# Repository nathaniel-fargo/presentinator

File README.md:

# the PRESENTINATOR

## Plot
Santa got a cold, and it's December 24th! As his top elf you gotta step it up\
You decide to make a cannon to launch presents from the North Pole all over the world.\
Each house will light up when it's clock strikes midnight and you must shoot your target to the correct one.\
The longer you hold the trigger, the further your present will be shot. You call it, "the PRESENTINATOR".\
(Depending on how well this goes, you might be in for a raise aftewards... and boy do you love Candy Canes)

## Project

There's hardware, graphics, and soon to be firmware in this repo.\
I initially designed this as a four layer board, but when I experimenting with deleting the inner layers, practically all the grounds were routed together besides a few floating islands. Everything should be low speed enough so that's fine.\
The project is powered off of two 2032s, with a switch, and then minimal polarity protection and then bucked down to 3.3V.\
The brains of the operation is the STM32F030F4, a very minimal STM microcontroller.\
Over I2C it drives the IS31FL3731-SA LED Matrix driver, which is not used to full capacity.\
There's also a capactive sense button IC, as well as the capability to drive a vibration motor for full haptic I/O.

## Status
Hardware: Designed\
Board: Being manufactured\
Firmware: Will be done by Christmas

## License
MIT Open Source License-inator

## Motivation
I have some younger people in my life and a habit of making DIY christmas presents. In the past they've been largely "crafty" (e.g. wood, leather) but this year I went all-in on electronics.

## Inspiration
Roughly inspired by the [light rail](https://github.com/nonik0/Light-Rail) PCB train track project, as well as Doofenshmirtz's naming conventions.

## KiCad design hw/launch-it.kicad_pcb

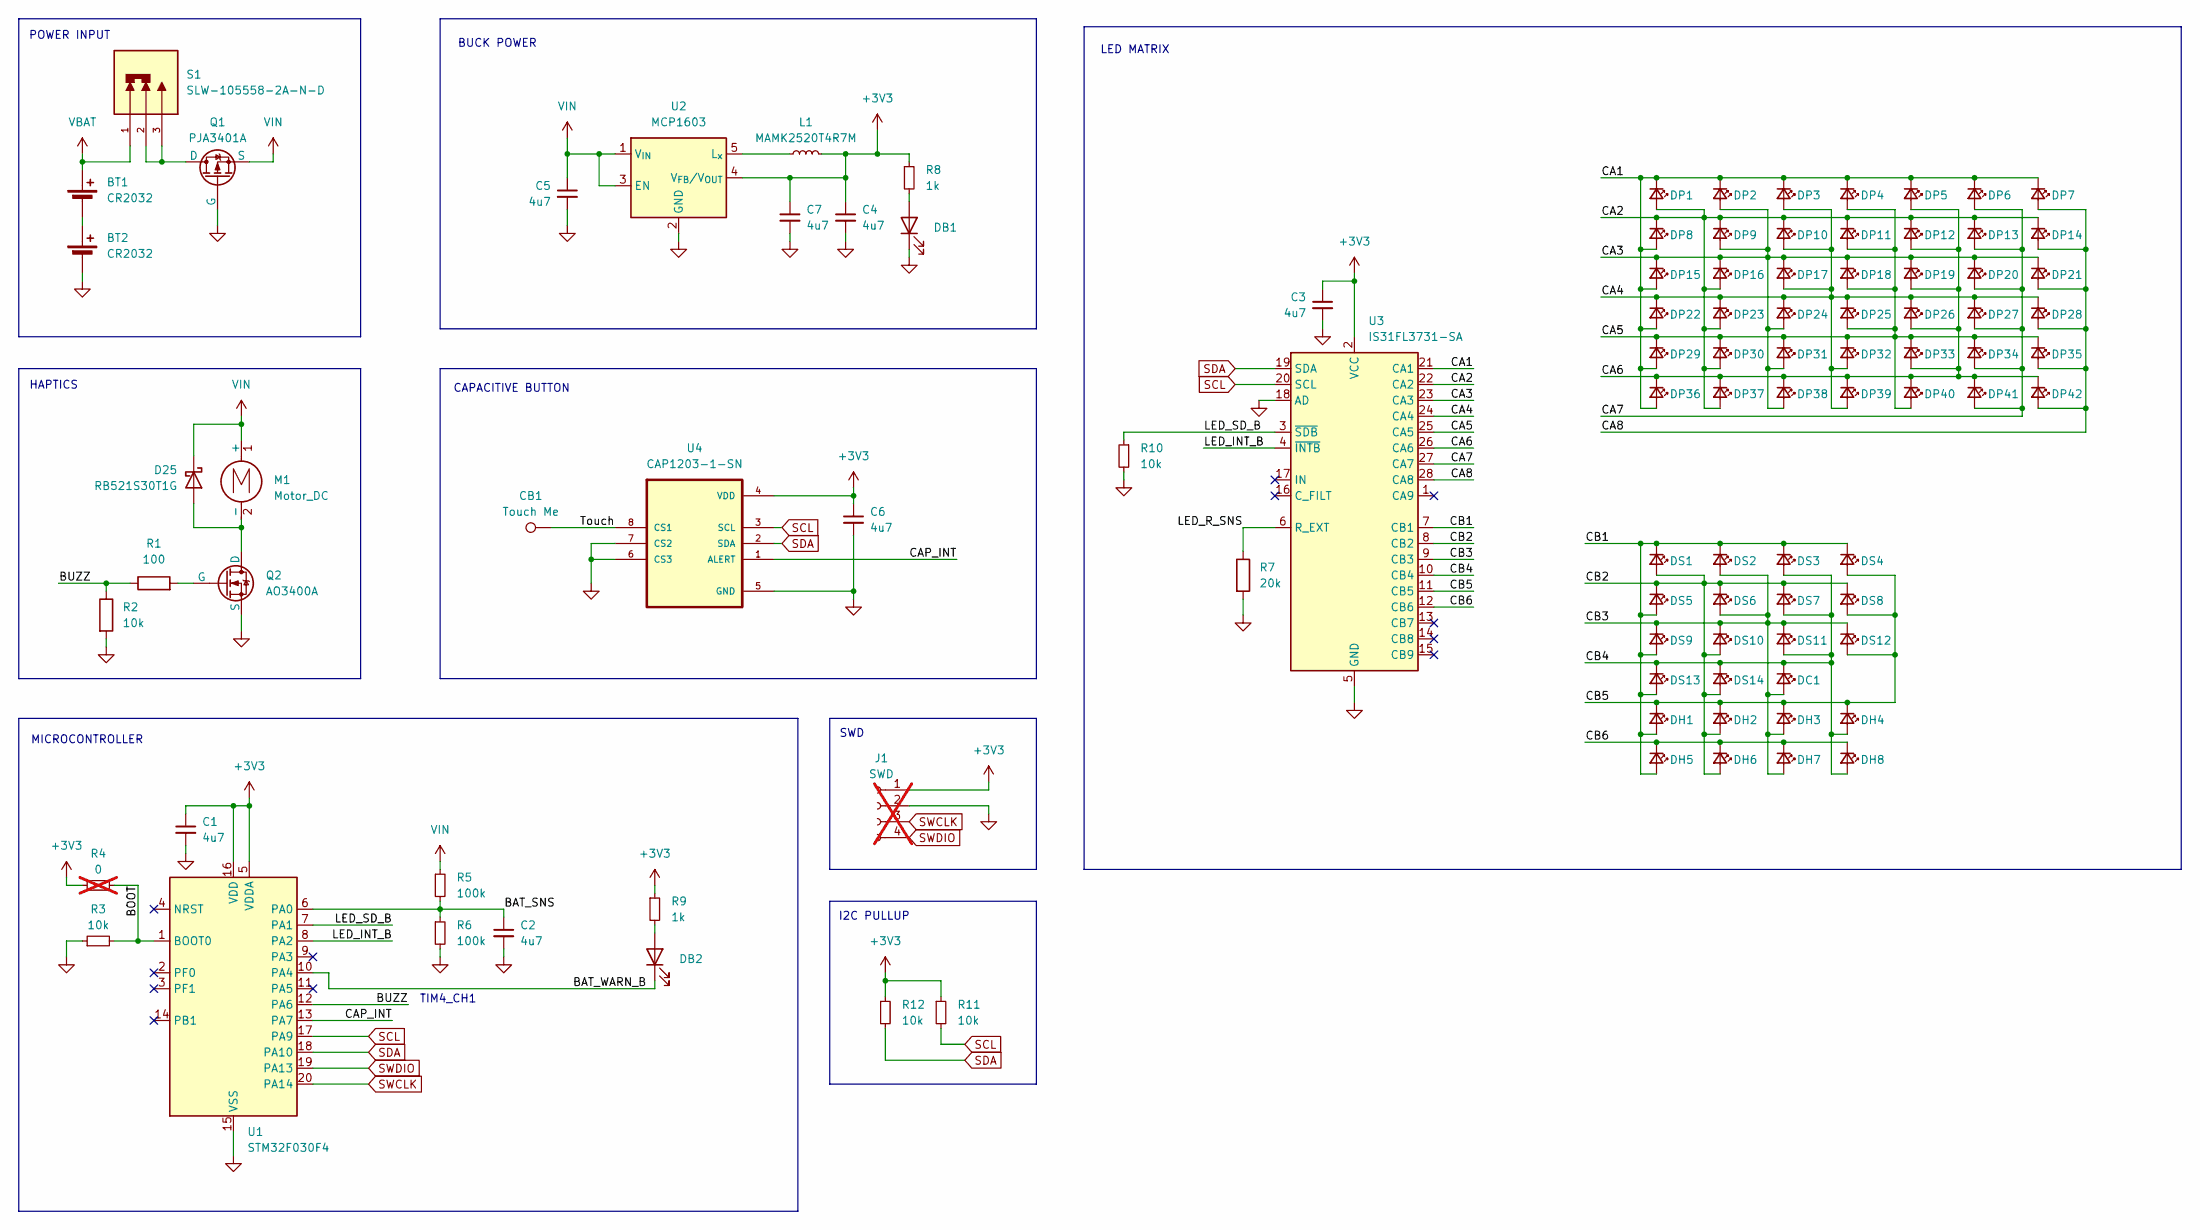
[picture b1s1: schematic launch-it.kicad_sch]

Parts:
BT1, BT2: CR2032; BAT_BAT-HLD-003-SMT
C1, C2, C3, C4, C5, C6, C7: 4u7; C_0402_1005Metric_Pad0.74x0.62mm_HandSolder
CB1: Touch Me; TestPoint_Pad_1.0x1.0mm
D25: RB521S30T1G; D_SOD-523
DB1, DB2: LED; LED_0805_2012Metric_InnerMarking
DC1: LED_Small; LED_0805_2012Metric_InnerMarking
DH1, DH2, DH3, DH4, DH5, DH6, DH7, DH8: LED_Small; LED_0805_2012Metric_InnerMarking
DP1, DP2, DP3, DP4, DP5, DP6, DP7, DP8, DP9, DP10, DP11, DP12, DP13, DP14, DP15, DP16, DP17, DP18, DP19, DP20, DP21, DP22, DP23, DP24, DP25, DP26, DP27, DP28, DP29, DP30, DP31, DP32, DP33, DP34, DP35, DP36, DP37, DP38, DP39, DP40, DP41, DP42: LED_Small; LED_0805_2012Metric_InnerMarking
DS1, DS2, DS3, DS4, DS5, DS6, DS7, DS8, DS9, DS10, DS11, DS12, DS13, DS14: LED_Small; LED_0402_1005Metric_Minimal
J1: SWD; PinHeader_1x04_P2.54mm_Vertical; not fitted
L1: MAMK2520T4R7M; L_1008_2520Metric_Pad1.43x2.20mm_HandSolder
M1: Motor_DC; PinHeader_1x02_P2.54mm_Vertical
Q1: PJA3401A; SOT-23-3
Q2: AO3400A; SOT-23-3
R1: 100; R_0402_1005Metric_Pad0.72x0.64mm_HandSolder
R2, R3, R10, R11, R12: 10k; R_0402_1005Metric_Pad0.72x0.64mm_HandSolder
R4: 0; R_0402_1005Metric_Pad0.72x0.64mm_HandSolder; not fitted
R5, R6: 100k; R_0402_1005Metric_Pad0.72x0.64mm_HandSolder
R7: 20k; R_0402_1005Metric_Pad0.72x0.64mm_HandSolder
R8, R9: 1k; R_0402_1005Metric_Pad0.72x0.64mm_HandSolder
S1: SLW-105558-2A-N-D; SW_SLW-105558-2A-N-D; PARTREV 1.01
U1: STM32F030F4; TSSOP-20_4.4x6.5mm_P0.65mm
U2: MCP1603; TSOT-23-5
U3: IS31FL3731-SA; SSOP-28_5.3x10.2mm_P0.65mm
U4: CAP1203-1-SN; SOIC127P600X175-8N

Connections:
+3V3: C1.1, C3.1, C4.1, C6.1, C7.1, J1.1, L1.2, R4.1, R8.1, R9.1, R11.1, R12.1, U1.5 (VDDA), U1.16 (VDD), U2.4 (V_{FB}/V_{OUT}), U3.2 (VCC), U4.4 (VDD)
/BAT_SNS: C2.1, R5.2, R6.1, U1.6 (PA0)
/BAT_WARN_B: DB2.1 (K), U1.10 (PA4)
/BOOT: R3.2, R4.2, U1.1 (BOOT0)
/BUZZ: R1.1, R2.1, U1.12 (PA6)
/CA1: DP1.1 (K), DP2.1 (K), DP3.1 (K), DP4.1 (K), DP5.1 (K), DP6.1 (K), DP7.1 (K), DP8.2 (A), DP15.2 (A), DP22.2 (A), DP29.2 (A), DP36.2 (A), U3.21 (CA1)
/CA2: DP1.2 (A), DP8.1 (K), DP9.1 (K), DP10.1 (K), DP11.1 (K), DP12.1 (K), DP13.1 (K), DP14.1 (K), DP16.2 (A), DP23.2 (A), DP30.2 (A), DP37.2 (A), U3.22 (CA2)
/CA3: DP2.2 (A), DP9.2 (A), DP15.1 (K), DP16.1 (K), DP17.1 (K), DP18.1 (K), DP19.1 (K), DP20.1 (K), DP21.1 (K), DP24.2 (A), DP31.2 (A), DP38.2 (A), U3.23 (CA3)
/CA4: DP3.2 (A), DP10.2 (A), DP17.2 (A), DP22.1 (K), DP23.1 (K), DP24.1 (K), DP25.1 (K), DP26.1 (K), DP27.1 (K), DP28.1 (K), DP32.2 (A), DP39.2 (A), U3.24 (CA4)
/CA5: DP4.2 (A), DP11.2 (A), DP18.2 (A), DP25.2 (A), DP29.1 (K), DP30.1 (K), DP31.1 (K), DP32.1 (K), DP33.1 (K), DP34.1 (K), DP35.1 (K), DP40.2 (A), U3.25 (CA5)
/CA6: DP5.2 (A), DP12.2 (A), DP19.2 (A), DP26.2 (A), DP33.2 (A), DP36.1 (K), DP37.1 (K), DP38.1 (K), DP39.1 (K), DP40.1 (K), DP41.1 (K), DP42.1 (K), U3.26 (CA6)
/CA7: DP6.2 (A), DP13.2 (A), DP20.2 (A), DP27.2 (A), DP34.2 (A), DP41.2 (A), U3.27 (CA7)
/CA8: DP7.2 (A), DP14.2 (A), DP21.2 (A), DP28.2 (A), DP35.2 (A), DP42.2 (A), U3.28 (CA8)
/CAP_INT: U1.13 (PA7), U4.1 (ALERT)
/CB1: DH1.2 (A), DH5.2 (A), DS1.1 (K), DS2.1 (K), DS3.1 (K), DS4.1 (K), DS5.2 (A), DS9.2 (A), DS13.2 (A), U3.7 (CB1)
/CB2: DH2.2 (A), DH6.2 (A), DS1.2 (A), DS5.1 (K), DS6.1 (K), DS7.1 (K), DS8.1 (K), DS10.2 (A), DS14.2 (A), U3.8 (CB2)
/CB3: DC1.2 (A), DH3.2 (A), DH7.2 (A), DS2.2 (A), DS6.2 (A), DS9.1 (K), DS10.1 (K), DS11.1 (K), DS12.1 (K), U3.9 (CB3)
/CB4: DC1.1 (K), DH4.2 (A), DH8.2 (A), DS3.2 (A), DS7.2 (A), DS11.2 (A), DS13.1 (K), DS14.1 (K), U3.10 (CB4)
/CB5: DH1.1 (K), DH2.1 (K), DH3.1 (K), DH4.1 (K), DS4.2 (A), DS8.2 (A), DS12.2 (A), U3.11 (CB5)
/CB6: DH5.1 (K), DH6.1 (K), DH7.1 (K), DH8.1 (K), U3.12 (CB6)
/LED_INT_B: U1.8 (PA2), U3.4 (~INTB)
/LED_R_SNS: R7.1, U3.6 (R_EXT)
/LED_SD_B: R10.1, U1.7 (PA1), U3.3 (~SDB)
/Touch: CB1.1, U4.8 (CS1)
GND: BT2.2 (-), C1.2, C2.2, C3.2, C4.2, C5.2, C6.2, C7.2, DB1.1 (K), J1.2, Q1.2 (G), Q2.3 (S), R2.2, R3.1, R6.2, R7.2, R10.2, U1.15 (VSS), U2.2 (GND), U3.5 (GND), U3.18 (AD), U4.5 (GND), U4.6 (CS3), U4.7 (CS2)
unnamed: BT1.2 (-), BT2.1 (+)
unnamed: D25.2 (A), M1.2 (-), Q2.1 (D)
unnamed: DB1.2 (A), R8.2
unnamed: DB2.2 (A), R9.2
unnamed: Q1.1 (D), S1.2, S1.3
unnamed: Q2.2 (G), R1.2
unnamed: L1.1, U2.5 (L_{x})
SCL: R11.2, U1.17 (PA9), U3.20 (SCL), U4.3 (SCL)
SDA: R12.2, U1.18 (PA10), U3.19 (SDA), U4.2 (SDA)
SWCLK: J1.3, U1.20 (PA14)
SWDIO: J1.4, U1.19 (PA13)
VBAT: BT1.1 (+), S1.1
VIN: C5.1, D25.1 (K), M1.1 (+), Q1.3 (S), R5.1, U2.1 (V_{IN}), U2.3 (EN)

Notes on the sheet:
POWER INPUT
HAPTICS
MICROCONTROLLER
I2C PULLUP
BUCK POWER
TIM4_CH1
LED MATRIX
SWD
CAPACITIVE BUTTON

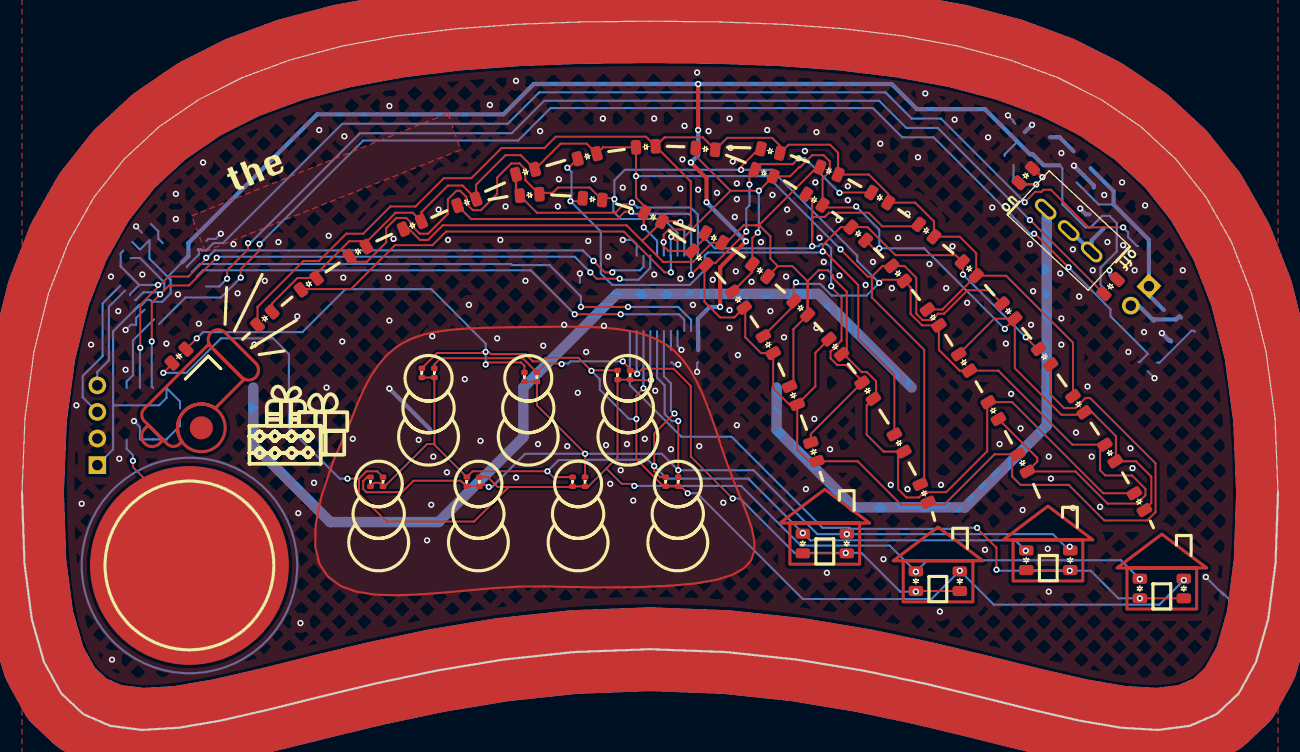
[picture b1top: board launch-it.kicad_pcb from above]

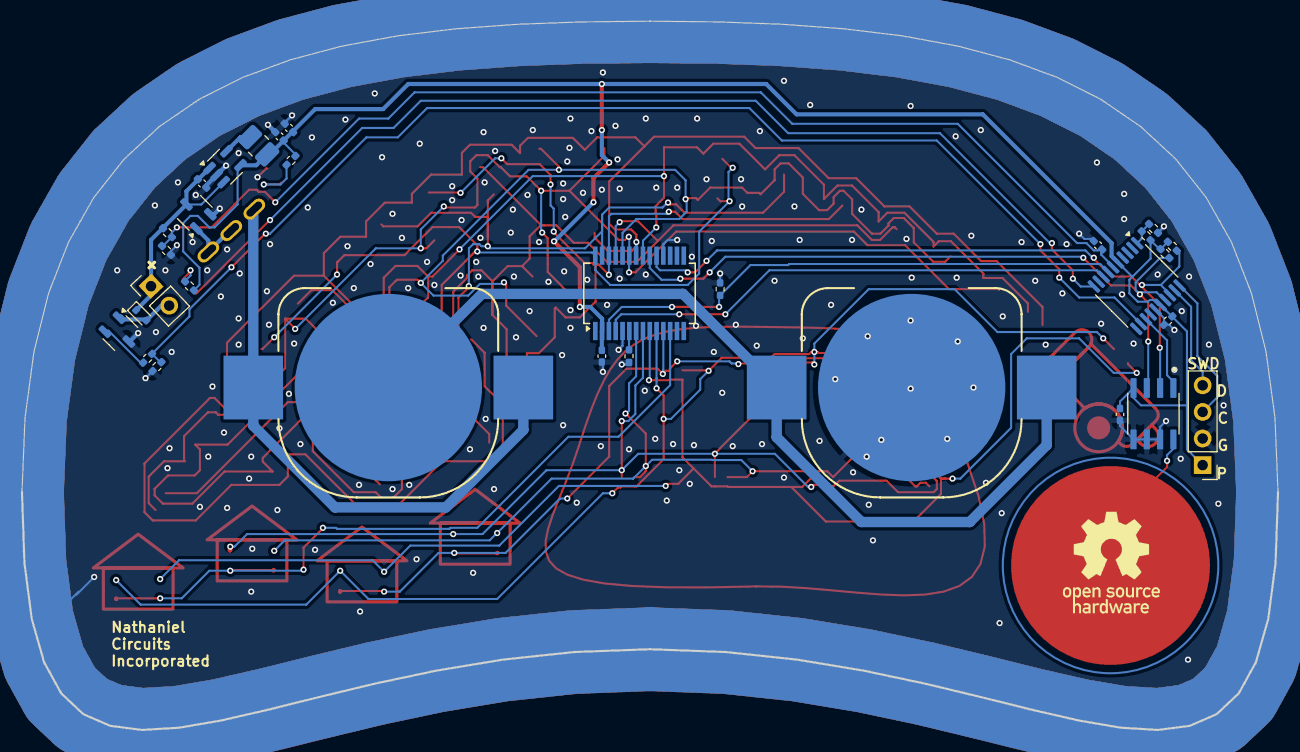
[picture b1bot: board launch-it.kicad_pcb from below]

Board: 2 copper layers, 120.0 x 67.6 mm, 100 parts (31 on the bottom side), 38 nets.

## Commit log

2025-11-28 Updated .gitignore
2025-11-28 Add MIT License to the project
2025-11-28 updated CR2032 PN and minimal layout updates
2025-11-29 added updated gerber (maybe unnecessary, idk)
